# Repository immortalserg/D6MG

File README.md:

# D6MG shield
## Палата расширения для OrangePi PC
### Описание
- питание от источника питания 12 В
- часы реального времени i2c DS3132
- 1-wire на шине i2c DS2482
- RS485
- CAN
- выведены порты LAN и 2 USB вниз
- 315/433 МГц приемники - передатчики (2 микросхемы SYN470R, 2 микросхемы SYN115)
- nrf24l01+
- zigbee (CC2530 с усилителем CC2591)
- LoRa RFM95 (модуль)
- RFM69 (модуль)
- 16 каналов ШИМ (PCA9685)
- 16 каналов входы/выходы (MCP27013)
- 16 каналов DAC (4 микросхемы MCP4728)
- 16 каналов ADC (4 микросхемы MCP3424)
- боковой разъем c шиной i2c для подключения модулей расширения Wiren Board
- USB - UART0 СP2102
- управляемый по GPIO кулер охлаждения

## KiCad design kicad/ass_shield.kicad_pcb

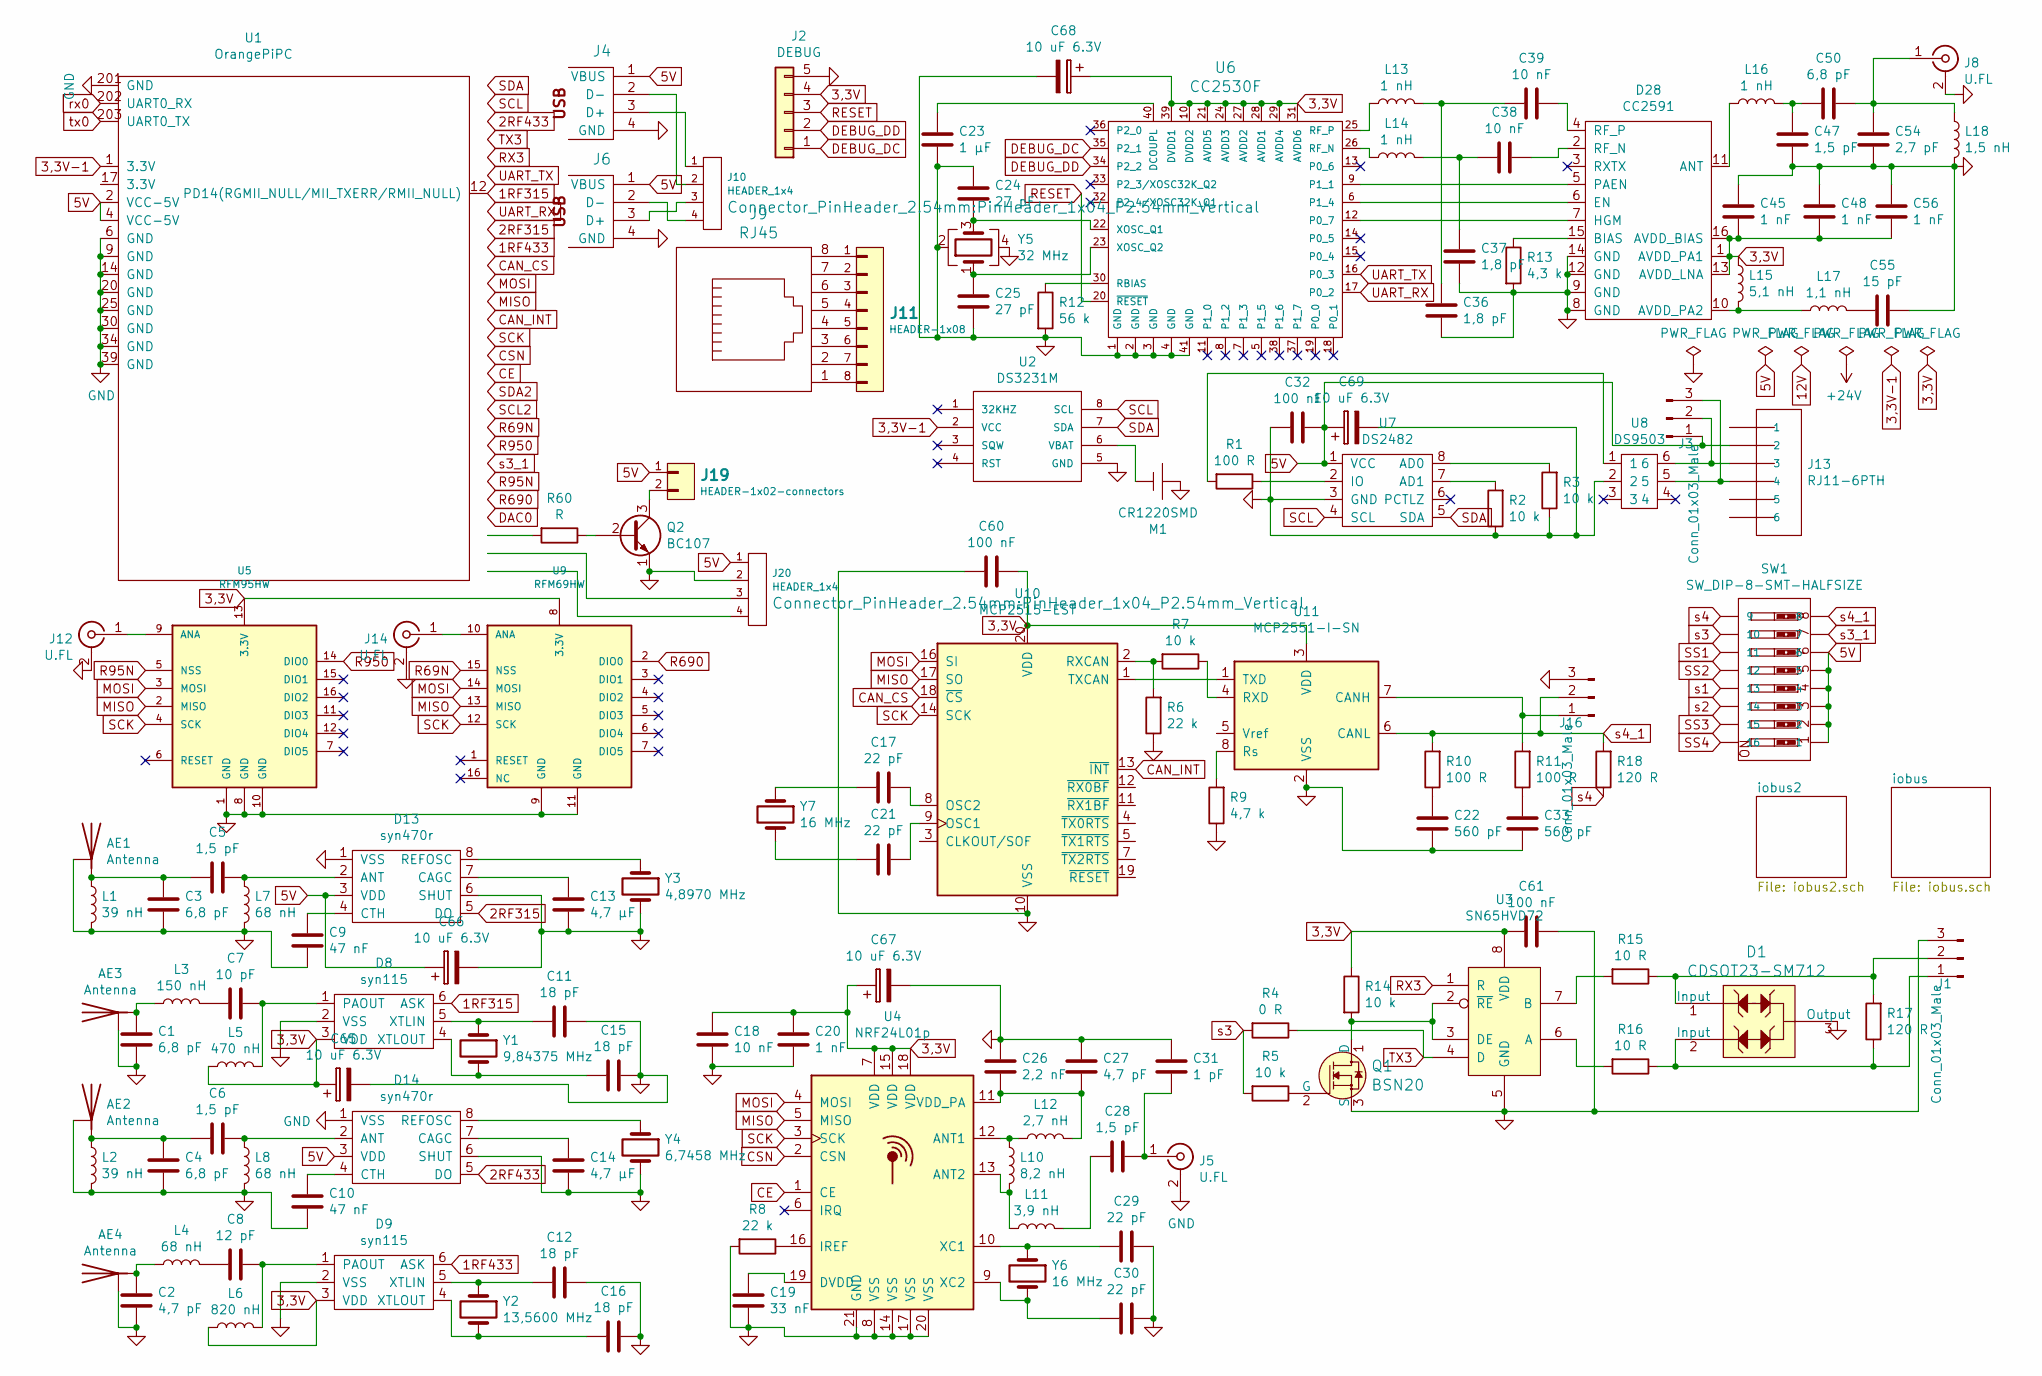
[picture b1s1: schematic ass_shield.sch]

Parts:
AE1, AE2, AE3, AE4: Antenna; U.FL_Hirose_U.FL-R-SMT-1_Vertical
C1, C3, C4, C50: 6,8 pF; C_0402_1005Metric
C2, C27: 4,7 pF; C_0402_1005Metric
C5, C6, C28, C47: 1,5 pF; C_0402_1005Metric
C7: 10 pF; C_0402_1005Metric
C8: 12 pF; C_0402_1005Metric
C9, C10: 47 nF; C_0402_1005Metric
C11, C12, C15, C16: 18 pF; C_0402_1005Metric
C13, C14: 4,7 µF; C_0402_1005Metric
C17, C21, C29, C30: 22 pF; C_0402_1005Metric
C18, C38, C39: 10 nF; C_0402_1005Metric
C19: 33 nF; C_0402_1005Metric
C20, C45, C48, C56: 1 nF; C_0402_1005Metric
C22, C33: 560 pF; C_0402_1005Metric
C23: 1 µF; C_0402_1005Metric
C24, C25: 27 pF; C_0402_1005Metric
C26: 2,2 nF; C_0402_1005Metric
C31: 1 pF; C_0402_1005Metric
C32, C60, C61: 100 nF; C_0402_1005Metric
C36, C37: 1,8 pF; C_0402_1005Metric
C54: 2,7 pF; C_0402_1005Metric
C55: 15 pF; C_0402_1005Metric
C65, C66, C67, C68, C69: 10 uF 6.3V; C_1206_3216Metric
D1: CDSOT23-SM712; SOT-23; MPN CDSOT23-SM712; Digi-Key_PN CDSOT23-SM712CT-ND
D8, D9: syn115; SOT-23-6_Handsoldering
D13, D14: syn470r; SSOP-8_3.95x5.21x3.27mm_P1.27mm
D28: CC2591; QFN-16-1EP_4x4mm_P0.65mm_EP2.5x2.5mm
J1, J3, J16: Conn_01x03_Male; pt_1,5-3-3,5-h
J2: DEBUG; PinHeader_1x05_P1.27mm_Vertical
J4, J6: USB; conn_usb_A-vert
J5, J8, J12, J14: U.FL; U.FL_Hirose_U.FL-R-SMT-1_Vertical
J9: RJ45; rj45-shield
J10, J20: HEADER_1x4; PinHeader_1x04_P2.54mm_Vertical
J11: HEADER-1x08; PinHeader_2x04_P2.54mm_Vertical
J13: RJ11-6PTH; rj11-shield
J19: HEADER-1x02-connectors; PinHeader_1x02_P2.54mm_Vertical
L1, L2: 39 nH; L_0402_1005Metric
L3: 150 nH; L_0402_1005Metric
L4, L7, L8: 68 nH; L_0402_1005Metric
L5: 470 nH; L_0603_1608Metric
L6: 820 nH; L_0805_2012Metric
L10: 8,2 nH; L_0402_1005Metric
L11: 3,9 nH; L_0402_1005Metric
L12: 2,7 nH; L_0402_1005Metric
L13, L14, L16: 1 nH; L_0402_1005Metric
L15: 5,1 nH; L_0402_1005Metric
L17: 1,1 nH; L_0402_1005Metric
L18: 1,5 nH; L_0402_1005Metric
M1: CR1220SMD; cr1220_smd
Q1: BSN20; SOT-23; MPN BS170; Digi-Key_PN BS170-ND
Q2: BC107; SOT-23
R1, R10, R11: 100 R; R_0402_1005Metric
R2, R3, R5, R7, R14: 10 k; R_0402_1005Metric
R4: 0 R; R_0402_1005Metric
R6, R8: 22 k; R_0402_1005Metric
R9: 4,7 k; R_0402_1005Metric
R12: 56 k; R_0402_1005Metric
R13: 4,3 k; R_0402_1005Metric
R15, R16: 10 R; R_0402_1005Metric
R17, R18: 120 R; R_0402_1005Metric
R60: R; R_0402_1005Metric
SW1: SW_DIP-8-SMT-HALFSIZE; DIPSWITCH-08-50MIL
U1: OrangePiPC
U2: DS3231M; SO-8_5.3x6.2mm_P1.27mm
U3: SN65HVD72; SOIC-8_3.9x4.9mm_P1.27mm
U4: NRF24L01p; QFN-20-1EP_4x4mm_P0.5mm_EP2.5x2.5mm
U5: RFM95HW; RFM69HW_SMD_Handsoldering
U6: CC2530F; QFN-40-1EP_6x6mm_P0.5mm_EP4.6x4.6mm
U7: DS2482; SOIC-8_3.9x4.9mm_P1.27mm
U8: DS9503; TSOT-23-6
U9: RFM69HW; RFM69HW_SMD_Handsoldering
U10: MCP2515-EST; TSSOP-20_4.4x6.5mm_P0.65mm
U11: MCP2551-I-SN; SOIC-8_3.9x4.9mm_P1.27mm
Y1: 9,84375 MHz; Crystal_HC49-4H_Vertical
Y2: 13,5600 MHz; Crystal_HC49-4H_Vertical
Y3: 4,8970 MHz; Crystal_HC49-4H_Vertical
Y4: 6,7458 MHz; Crystal_HC49-4H_Vertical
Y5: 32 MHz; Crystal_SMD_3225-4Pin_3.2x2.5mm
Y6, Y7: 16 MHz; Crystal_SMD_3215-2Pin_3.2x1.5mm

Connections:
1RF315: D8.6 (ASK), U1.12 (PD14(RGMII_NULL/MII_TXERR/RMII_NULL))
1RF433: D9.6 (ASK), U1.16
2RF315: D13.5 (DO), U1.15
2RF433: D14.5 (DO), U1.7
3,3V: C18.1, C20.1, C45.1, C48.1, C56.1, C60.1, C61.2, C65.1, C67.1, C68.1, D8.3 (VDD), D9.3 (VDD), D28.1 (AVDD_PA1), D28.13 (AVDD_LNA), D28.16 (AVDD_BIAS), J2.4, L5.1, L6.1, L15.1, R14.1, U3.8 (VDD), U4.7 (VDD), U4.15 (VDD), U4.18 (VDD), U5.13 (3.3V), U6.10 (DVDD2), U6.21 (AVDD5), U6.24 (AVDD3), U6.27 (AVDD2), U6.28 (AVDD1), U6.29 (AVDD4), U6.31 (AVDD6), U6.39 (DVDD1), U9.8 (3.3V), U10.20 (VDD), U11.3 (VDD); also elsewhere on the board
3,3V-1: U1.1 (3.3V), U2.2 (VCC)
5V: C32.1, C66.1, C69.1, D13.3 (VDD), D14.3 (VDD), J3.1, J4.1 (VBUS), J6.1 (VBUS), J13.2, J19.1, J20.1, SW1.1, SW1.2, SW1.3, SW1.4, SW1.5, SW1.6, U1.2 (VCC-5V), U1.4 (VCC-5V), U7.1 (VCC); also elsewhere on the board
CAN_CS: U1.18, U10.18 (~CS)
CAN_INT: U1.22, U10.13 (~INT)
CE: U1.26, U4.1 (CE)
CSN: U1.24, U4.2 (CSN)
DAC0: U1.36; also elsewhere on the board
DEBUG_DC: J2.1, U6.35 (P2_1)
DEBUG_DD: J2.2, U6.34 (P2_2)
GND: AE1.2 (GND), AE2.2 (GND), AE3.2 (GND), AE4.2 (GND), C1.1, C2.1, C3.2, C4.2, C9.2, C10.2, C11.1, C12.1, C13.1, C14.1, C15.1, C16.1, C18.2, C19.2, C20.2, C22.1, C23.2, C24.1, C25.2, C26.1, C27.1, C29.1, C30.1, C31.1, C32.2, C33.1, C36.2, C37.2, C45.2, C47.1, C48.2, C54.1, C55.1, C56.2, C60.2, C61.1, C65.2, C66.2, C67.2, C68.2, C69.2, D1.3 (Output), D8.2 (VSS), D9.2 (VSS), D13.1 (VSS), D13.6 (SHUT), D14.1 (VSS), D14.6 (SHUT), D28.8 (GND), D28.9 (GND), D28.12 (GND), D28.14 (GND), J1.3, J2.5, J4.4 (GND), J5.2 (Ext), J6.4 (GND), J8.2 (Ext), J12.2 (Ext), J14.2 (Ext), J16.3, J20.2, L1.2, L2.2, L7.2, L8.2, L18.2, M1.2 (+), Q1.3 (S), Q2.1 (E), R2.1, R3.1, R6.1, R8.2, R9.1, R12.2, R13.2, U1.6 (GND), U1.9 (GND), U1.14 (GND), U1.20 (GND), U1.25 (GND), U1.30 (GND), U1.34 (GND), U1.39 (GND), U1.201 (GND), U2.5 (GND), U3.5 (GND), U4.8 (VSS), U4.14 (VSS), U4.17 (VSS), U4.20 (VSS), U4.21 (GND), U5.1 (GND), U5.8 (GND), U5.10 (GND), U6.1 (GND), U6.2 (GND), U6.3 (GND), U6.4 (GND), U6.41 (GND), U7.3 (GND), U8.2, U9.9 (GND), U9.11 (GND), U10.10 (VSS), U11.2 (VSS), Y3.2, Y4.2, Y5.2, Y5.4; also elsewhere on the board
MISO: U1.21, U4.5 (MISO), U5.2 (MISO), U9.13 (MISO), U10.17 (SO)
MOSI: U1.19, U4.4 (MOSI), U5.3 (MOSI), U9.14 (MOSI), U10.16 (SI)
unnamed: AE1.1 (A), C3.1, C5.2, L1.1
unnamed: AE2.1 (A), C4.1, C6.2, L2.1
unnamed: AE3.1 (A), C1.2, L3.1
unnamed: AE4.1 (A), C2.2, L4.1
unnamed: C5.1, D13.2 (ANT), L7.1
unnamed: C6.1, D14.2 (ANT), L8.1
unnamed: C7.1, D8.1 (PAOUT), L5.2
unnamed: C7.2, L3.2
unnamed: C8.1, D9.1 (PAOUT), L6.2
unnamed: C8.2, L4.2
unnamed: C9.1, D13.4 (CTH)
unnamed: C10.1, D14.4 (CTH)
unnamed: C11.2, D8.5 (XTLIN), Y1.1
unnamed: C12.2, D9.5 (XTLIN), Y2.1
unnamed: C13.2, D13.7 (CAGC)
unnamed: C14.2, D14.7 (CAGC)
unnamed: C15.2, D8.4 (XTLOUT), Y1.2
unnamed: C16.2, D9.4 (XTLOUT), Y2.2
unnamed: C17.1, U10.8 (OSC2)
unnamed: C17.2, Y7.1
unnamed: C19.1, U4.19 (DVDD)
unnamed: C21.1, U10.9 (OSC1)
unnamed: C21.2, Y7.2
unnamed: C22.2, R10.1
unnamed: C23.1, U6.40 (DCOUPL)
unnamed: C24.2, U6.22 (XOSC_Q1), Y5.3
unnamed: C25.1, U6.23 (XOSC_Q2), Y5.1
unnamed: C26.2, C27.2, L12.2, U4.11 (VDD_PA)
unnamed: C28.1, C31.2, J5.1 (In)
unnamed: C28.2, L11.2
unnamed: C29.2, U4.10 (XC1), Y6.1
unnamed: C30.2, U4.9 (XC2), Y6.2
unnamed: C33.2, R11.1
unnamed: C36.1, C39.2, L13.2
unnamed: C37.1, C38.2, L14.2
unnamed: C38.1, D28.2 (RF_N)
unnamed: C39.1, D28.4 (RF_P)
unnamed: C47.2, C50.2, L16.2
unnamed: C50.1, C54.2, J8.1 (In), L18.1
unnamed: C55.2, L17.2
unnamed: D1.1 (Input), J1.2, R15.1, R17.2
unnamed: D1.2 (Input), J1.1, R16.1, R17.1
unnamed: D13.8 (REFOSC), Y3.1
unnamed: D14.8 (REFOSC), Y4.1
unnamed: D28.5 (PAEN), U6.9 (P1_1)
unnamed: D28.6 (EN), U6.6 (P1_4)
unnamed: D28.7 (HGM), U6.12 (P0_7)
unnamed: D28.10 (AVDD_PA2), L15.2, L17.1
unnamed: D28.11 (ANT), L16.1
unnamed: D28.15 (BIAS), R13.1
unnamed: J4.3 (D+), J10.1
unnamed: J4.2 (D-), J10.2
unnamed: J6.3 (D+), J10.3
unnamed: J6.2 (D-), J10.4
unnamed: J9.8, J11.1
unnamed: J9.7, J11.2
unnamed: J9.6, J11.3
unnamed: J9.5, J11.4
unnamed: J9.4, J11.5
unnamed: J9.3, J11.6
unnamed: J9.2, J11.7
unnamed: J9.1, J11.8
unnamed: J12.1 (In), U5.9 (ANA)
unnamed: J3.2, J13.3, U8.6
unnamed: J3.3, J13.4, U8.5
unnamed: J14.1 (In), U9.10 (ANA)
unnamed: J16.1, R11.2, U11.7 (CANH)
unnamed: J19.2, Q2.3 (C)
unnamed: J20.3, U1.38
unnamed: J20.4, U1.40
unnamed: L10.1, L12.1, U4.12 (ANT1)
unnamed: L10.2, L11.1, U4.13 (ANT2)
unnamed: L13.1, U6.25 (RF_P)
unnamed: L14.1, U6.26 (RF_N)
unnamed: M1.1 (-), U2.6 (VBAT)
unnamed: Q1.1 (D), R14.2, U3.2 (~RE), U3.3 (DE)
unnamed: Q1.2 (G), R5.1
unnamed: Q2.2 (B), R60.1
unnamed: R1.1, U7.2 (IO)
unnamed: R1.2, U8.1
unnamed: R2.2, U7.7 (AD1)
unnamed: R3.2, U7.8 (AD0)
unnamed: R6.2, R7.2, U10.2 (RXCAN)
unnamed: R7.1, U11.4 (RXD)
unnamed: R8.1, U4.16 (IREF)
unnamed: R9.2, U11.8 (Rs)
unnamed: R12.1, U6.30 (RBIAS)
unnamed: R15.2, U3.7 (B)
unnamed: R16.2, U3.6 (A)
unnamed: R60.2, U1.37
unnamed: U10.1 (TXCAN), U11.1 (TXD)
R69N: U1.29, U9.15 (NSS)
R95N: U1.33, U5.5 (NSS)
R690: U1.35, U9.2 (DIO0)
R950: U1.31, U5.14 (DIO0)
RESET: J2.3, U6.20 (~RESET)
RX3: U1.10, U3.1 (R)
SCK: U1.23, U4.3 (SCK), U5.4 (SCK), U9.12 (SCK), U10.14 (SCK)
SCL: U1.5, U2.8 (SCL), U7.4 (SCL); also elsewhere on the board
SCL2: U1.28; also elsewhere on the board
SDA: U1.3, U2.7 (SDA), U7.5 (SDA); also elsewhere on the board
SDA2: U1.27; also elsewhere on the board
SS1: SW1.11; also elsewhere on the board
SS2: SW1.12; also elsewhere on the board
SS3: SW1.15; also elsewhere on the board
SS4: SW1.16; also elsewhere on the board
TX3: R4.1, U1.8, U3.4 (D)
UART_RX: U1.13, U6.17 (P0_2)
UART_TX: U1.11, U6.16 (P0_3)
rx0: U1.202 (UART0_RX); also elsewhere on the board
s1: SW1.13; also elsewhere on the board
s2: SW1.14; also elsewhere on the board
s3: R4.2, R5.2, SW1.10
s3_1: SW1.7, U1.32
s4: R18.1, SW1.9
s4_1: J16.2, R10.2, R18.2, SW1.8, U11.6 (CANL)
tx0: U1.203 (UART0_TX); also elsewhere on the board

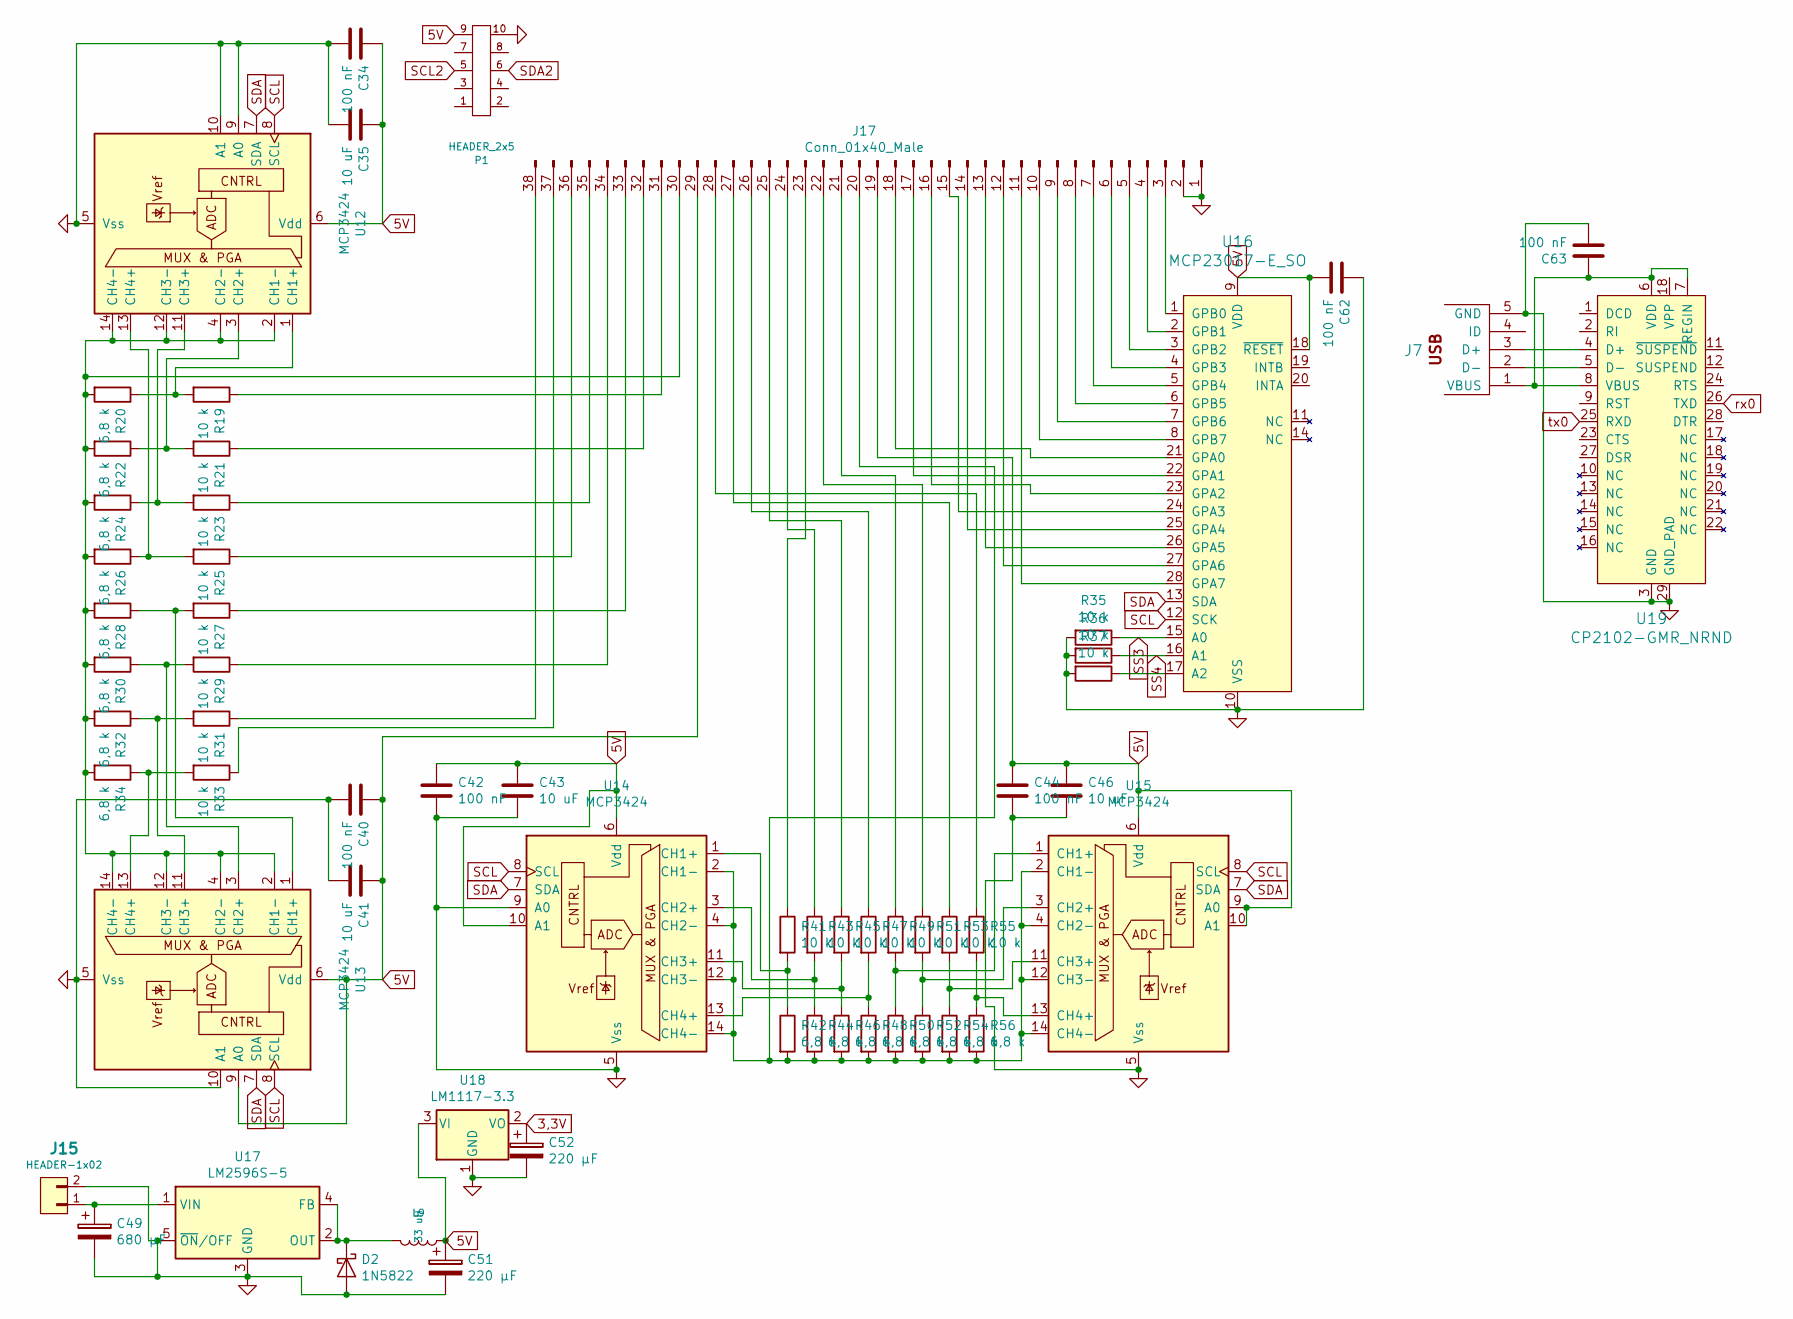
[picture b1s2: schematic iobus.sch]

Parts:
C34, C40, C42, C44, C62, C63: 100 nF; C_0402_1005Metric
C35, C41, C43, C46: 10 uF; C_0402_1005Metric
C49: 680 µF; CP_Elec_10x10
C51: 220 µF; CP_Elec_10x10
C52: 220 µF; C_1210_3225Metric
D2: 1N5822; D_SMC
J7: USBMINI; USB_Micro-B_Wuerth_614105150721_Vertical
J15: HEADER-1x02; mkds_1,5-2
J17: Conn_01x40_Male; PinHeader_2x19_P2.54mm_Vertical
L9: 33 uH; L_Bourns_SRR1260
P1: HEADER_2x5; PinSocket_2x05_P2.54mm_Horizontal
R19, R21, R23, R25, R27, R29, R31, R33, R35, R36, R37, R41, R43, R45, R47, R49, R51, R53, R55: 10 k; R_0402_1005Metric
R20, R22, R24, R26, R28, R30, R32, R34, R42, R44, R46, R48, R50, R52, R54, R56: 6,8 k; R_0402_1005Metric
U12, U13, U14, U15: MCP3424; TSSOP-14_4.4x5mm_P0.65mm
U16: MCP23017-E_SO; SOIC-28W_7.5x17.9mm_P1.27mm; MPN MCP23017-E/SO; Digi-Key_PN MCP23017-E/SO-ND
U17: LM2596S-5; TO-263-5_TabPin3
U18: LM1117-3.3; SOT-223
U19: CP2102-GMR_NRND; QFN-28-1EP_5x5mm_P0.5mm_EP3.35x3.35mm; MPN CP2102-GMR; Digi-Key_PN 336-1160-1-ND

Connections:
3,3V: C52.1, U18.2 (VO); also elsewhere on the board
5V: C34.1, C35.1, C40.1, C41.1, C42.1, C43.1, C44.1, C46.1, C51.1, C62.2, J17.19, J17.29, L9.1, P1.9, U12.6 (Vdd), U13.6 (Vdd), U13.9 (A0), U14.6 (Vdd), U14.10 (A1), U15.6 (Vdd), U15.9 (A0), U15.10 (A1), U16.9 (VDD), U16.18 (~RESET), U18.3 (VI); also elsewhere on the board
GND: C34.2, C35.2, C40.2, C41.2, C42.2, C43.2, C44.2, C46.2, C49.2, C51.2, C52.2, C62.1, C63.2, D2.2 (A), J7.5 (GND), J15.2, J17.1, J17.2, P1.10, R35.2, R36.2, R37.2, U12.5 (Vss), U12.9 (A0), U12.10 (A1), U13.5 (Vss), U13.10 (A1), U14.5 (Vss), U14.9 (A0), U15.5 (Vss), U16.10 (VSS), U17.3 (GND), U17.5 (~ON~/OFF), U18.1 (GND), U19.3 (GND), U19.29 (GND_PAD); also elsewhere on the board
unnamed: C49.1, J15.1, U17.1 (VIN)
unnamed: C63.1, J7.1 (VBUS), U19.6 (VDD), U19.7 (REGIN), U19.8 (VBUS)
unnamed: D2.1 (K), L9.2, U17.2 (OUT), U17.4 (FB)
unnamed: J7.2 (D-), U19.5 (D-)
unnamed: J7.3 (D+), U19.4 (D+)
unnamed: J17.3, U16.1 (GPB0)
unnamed: J17.4, U16.2 (GPB1)
unnamed: J17.5, U16.3 (GPB2)
unnamed: J17.6, U16.4 (GPB3)
unnamed: J17.7, U16.5 (GPB4)
unnamed: J17.8, U16.6 (GPB5)
unnamed: J17.9, U16.7 (GPB6)
unnamed: J17.10, U16.8 (GPB7)
unnamed: J17.11, U16.28 (GPA7)
unnamed: J17.12, U16.27 (GPA6)
unnamed: J17.13, U16.26 (GPA5)
unnamed: J17.14, U16.25 (GPA4)
unnamed: J17.15, U16.24 (GPA3)
unnamed: J17.16, U16.23 (GPA2)
unnamed: J17.17, U16.22 (GPA1)
unnamed: J17.18, U16.21 (GPA0)
unnamed: J17.20, R42.2, R44.2, R46.2, R48.2, R50.2, R52.2, R54.2, R56.2, U14.2 (CH1-), U14.4 (CH2-), U14.12 (CH3-), U14.14 (CH4-), U15.2 (CH1-), U15.4 (CH2-), U15.12 (CH3-), U15.14 (CH4-)
unnamed: J17.21, R49.1
unnamed: J17.22, R51.1
unnamed: J17.23, R41.1
unnamed: J17.24, R43.1
unnamed: J17.25, R45.1
unnamed: J17.26, R47.1
unnamed: J17.27, R53.1
unnamed: J17.28, R55.1
unnamed: J17.30, R20.2, R22.2, R24.2, R26.2, R28.2, R30.2, R32.2, R34.2, U12.2 (CH1-), U12.4 (CH2-), U12.12 (CH3-), U12.14 (CH4-), U13.2 (CH1-), U13.4 (CH2-), U13.12 (CH3-), U13.14 (CH4-)
unnamed: J17.31, R19.1
unnamed: J17.32, R21.1
unnamed: J17.33, R27.1
unnamed: J17.34, R29.1
unnamed: J17.35, R23.1
unnamed: J17.36, R25.1
unnamed: J17.37, R33.1
unnamed: J17.38, R31.1
unnamed: R19.2, R20.1, U12.1 (CH1+)
unnamed: R21.2, R22.1, U12.3 (CH2+)
unnamed: R23.2, R24.1, U12.11 (CH3+)
unnamed: R25.2, R26.1, U12.13 (CH4+)
unnamed: R27.2, R28.1, U13.1 (CH1+)
unnamed: R29.2, R30.1, U13.3 (CH2+)
unnamed: R31.2, R32.1, U13.11 (CH3+)
unnamed: R33.2, R34.1, U13.13 (CH4+)
unnamed: R37.1, U16.17 (A2)
unnamed: R41.2, R42.1, U14.1 (CH1+)
unnamed: R43.2, R44.1, U14.3 (CH2+)
unnamed: R45.2, R46.1, U14.11 (CH3+)
unnamed: R47.2, R48.1, U14.13 (CH4+)
unnamed: R49.2, R50.1, U15.1 (CH1+)
unnamed: R51.2, R52.1, U15.3 (CH2+)
unnamed: R53.2, R54.1, U15.11 (CH3+)
unnamed: R55.2, R56.1, U15.13 (CH4+)
SCL: U12.8 (SCL), U13.8 (SCL), U14.8 (SCL), U15.8 (SCL), U16.12 (SCK); also elsewhere on the board
SCL2: P1.5; also elsewhere on the board
SDA: U12.7 (SDA), U13.7 (SDA), U14.7 (SDA), U15.7 (SDA), U16.13 (SDA); also elsewhere on the board
SDA2: P1.6; also elsewhere on the board
SS3: R35.1, U16.15 (A0); also elsewhere on the board
SS4: R36.1, U16.16 (A1); also elsewhere on the board
rx0: U19.26 (TXD); also elsewhere on the board
tx0: U19.25 (RXD); also elsewhere on the board

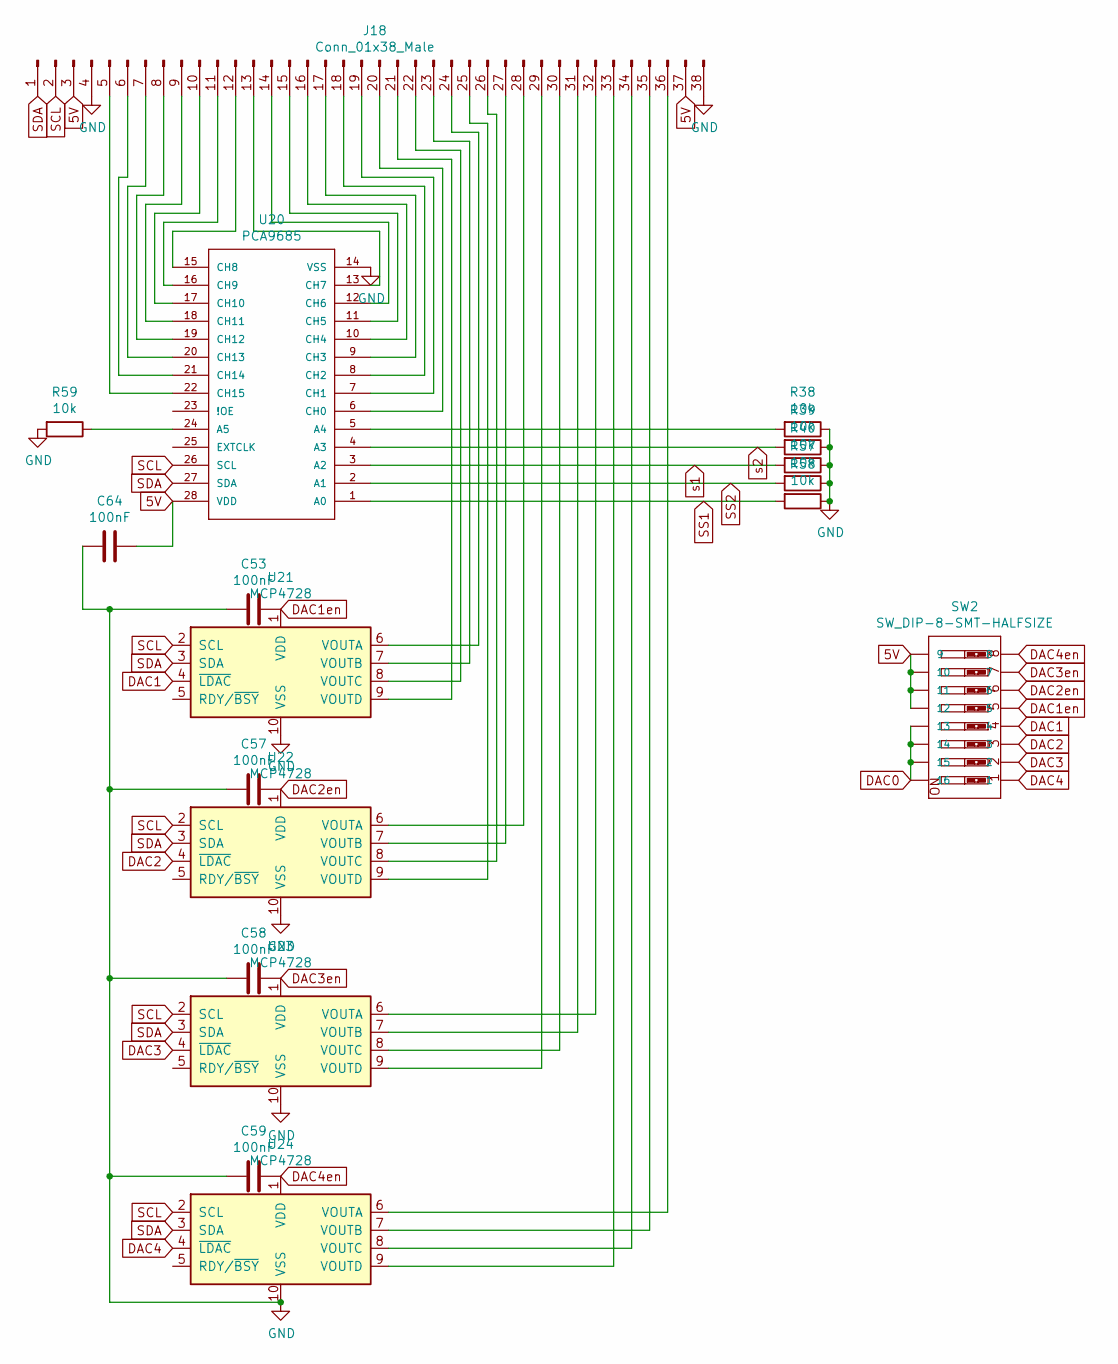
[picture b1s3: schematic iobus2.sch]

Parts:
C53, C57, C58, C59, C64: 100nF; C_0402_1005Metric
J18: Conn_01x38_Male; PinHeader_2x19_P2.54mm_Vertical
R38, R39, R40, R57, R58, R59: 10k; R_0402_1005Metric
SW2: SW_DIP-8-SMT-HALFSIZE; DIPSWITCH-08-50MIL
U20: PCA9685; TSSOP-28_4.4x9.7mm_P0.65mm
U21, U22, U23, U24: MCP4728; MSOP-10_3x3mm_P0.5mm

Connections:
5V: C64.1, J18.3, J18.37, SW2.9, SW2.10, SW2.11, SW2.12, U20.28 (VDD); also elsewhere on the board
DAC0: SW2.13, SW2.14, SW2.15, SW2.16; also elsewhere on the board
DAC1: SW2.4, U21.4 (~LDAC)
DAC1en: C53.1, SW2.5, U21.1 (VDD)
DAC2: SW2.3, U22.4 (~LDAC)
DAC2en: C57.1, SW2.6, U22.1 (VDD)
DAC3: SW2.2, U23.4 (~LDAC)
DAC3en: C58.1, SW2.7, U23.1 (VDD)
DAC4: SW2.1, U24.4 (~LDAC)
DAC4en: C59.1, SW2.8, U24.1 (VDD)
GND: C53.2, C57.2, C58.2, C59.2, C64.2, J18.4, J18.38, R38.1, R39.1, R40.1, R57.1, R58.1, R59.2, U20.14 (VSS), U21.10 (VSS), U22.10 (VSS), U23.10 (VSS), U24.10 (VSS); also elsewhere on the board
unnamed: J18.5, U20.22 (CH15)
unnamed: J18.6, U20.21 (CH14)
unnamed: J18.7, U20.20 (CH13)
unnamed: J18.8, U20.19 (CH12)
unnamed: J18.9, U20.18 (CH11)
unnamed: J18.10, U20.17 (CH10)
unnamed: J18.11, U20.16 (CH9)
unnamed: J18.12, U20.15 (CH8)
unnamed: J18.13, U20.13 (CH7)
unnamed: J18.14, U20.12 (CH6)
unnamed: J18.15, U20.11 (CH5)
unnamed: J18.16, U20.10 (CH4)
unnamed: J18.17, U20.9 (CH3)
unnamed: J18.18, U20.8 (CH2)
unnamed: J18.19, U20.7 (CH1)
unnamed: J18.20, U20.6 (CH0)
unnamed: J18.21, U21.9 (VOUTD)
unnamed: J18.22, U21.8 (VOUTC)
unnamed: J18.23, U21.7 (VOUTB)
unnamed: J18.24, U21.6 (VOUTA)
unnamed: J18.25, U22.9 (VOUTD)
unnamed: J18.26, U22.8 (VOUTC)
unnamed: J18.27, U22.7 (VOUTB)
unnamed: J18.28, U22.6 (VOUTA)
unnamed: J18.29, U23.9 (VOUTD)
unnamed: J18.30, U23.8 (VOUTC)
unnamed: J18.31, U23.7 (VOUTB)
unnamed: J18.32, U23.6 (VOUTA)
unnamed: J18.33, U24.9 (VOUTD)
unnamed: J18.34, U24.8 (VOUTC)
unnamed: J18.35, U24.7 (VOUTB)
unnamed: J18.36, U24.6 (VOUTA)
unnamed: R38.2, U20.5 (A4)
unnamed: R59.1, U20.24 (A5)
SCL: J18.2, U20.26 (SCL), U21.2 (SCL), U22.2 (SCL), U23.2 (SCL), U24.2 (SCL); also elsewhere on the board
SDA: J18.1, U20.27 (SDA), U21.3 (SDA), U22.3 (SDA), U23.3 (SDA), U24.3 (SDA); also elsewhere on the board
SS1: R58.2, U20.1 (A0); also elsewhere on the board
SS2: R57.2, U20.2 (A1); also elsewhere on the board
s1: R40.2, U20.3 (A2); also elsewhere on the board
s2: R39.2, U20.4 (A3); also elsewhere on the board

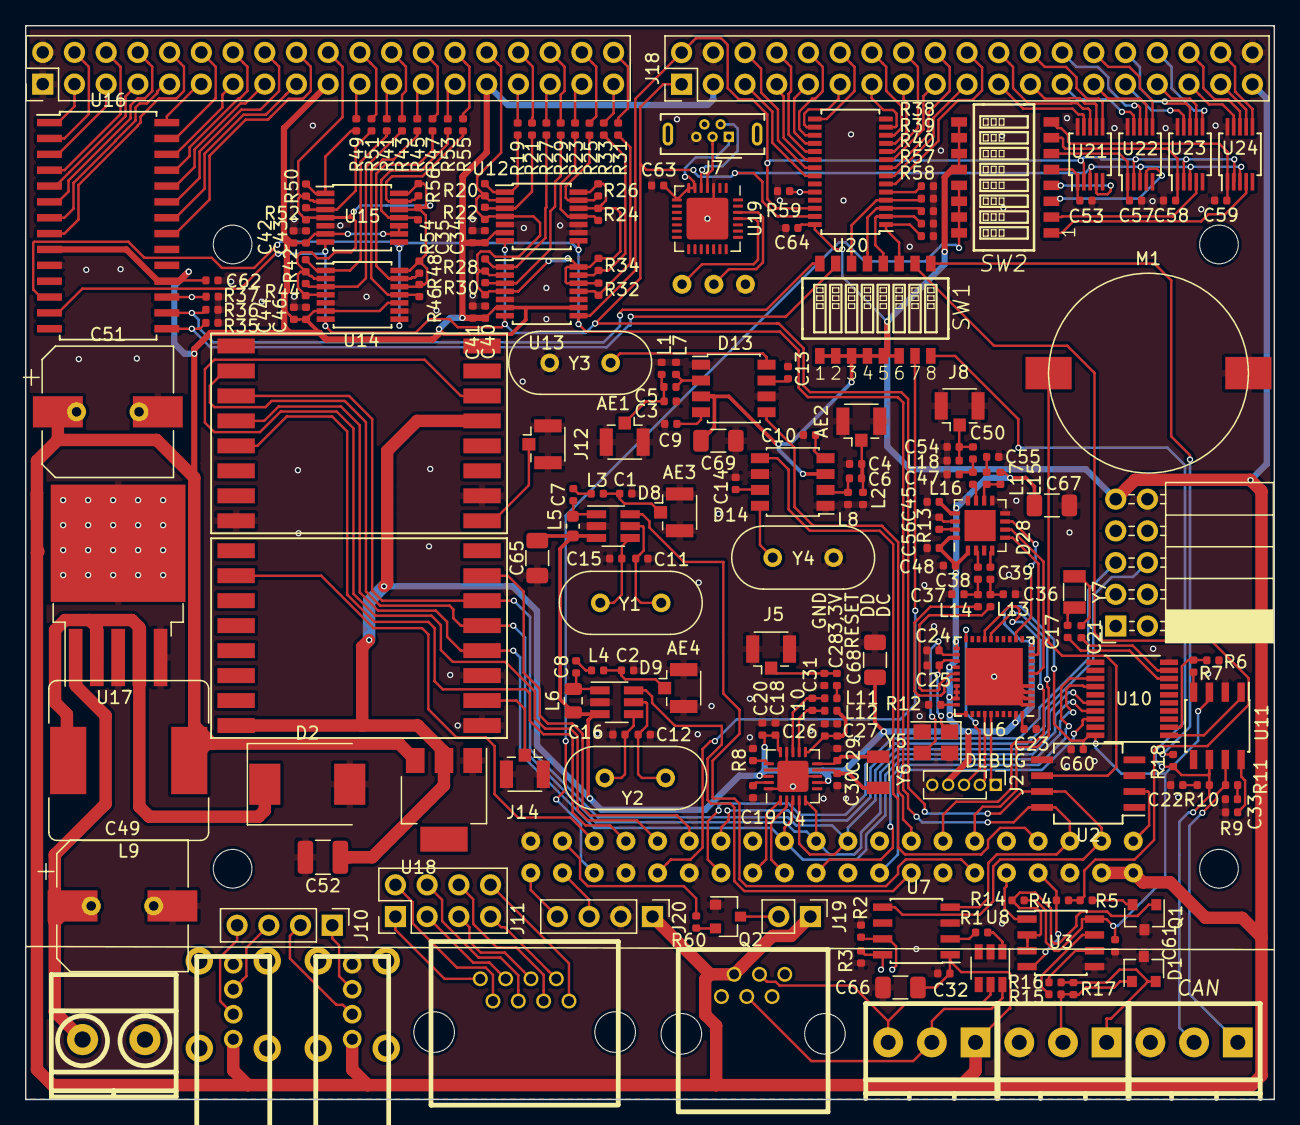
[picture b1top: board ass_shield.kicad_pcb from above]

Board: 2 copper layers, 100.0 x 86.0 mm, 215 parts (0 on the bottom side), 232 nets.

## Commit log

2018-11-01 a msg
